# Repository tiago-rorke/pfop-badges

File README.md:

# Badges from Other Planets

I made these supercapacitor powered badges for [Nowhere 2019](https://www.goingnowhere.org/), a regional burn near Zaragoza, Spain, for our fledgling barrio "People from Other Planets".

I wanted to try to use supercapacitors to avoid consuming hundreds of non-rechargeable coin cell batteries whilst keeping the design as simple as possible. Because 5V supercaps are considerably more expensive, I've used a pair of 2.5V caps in series, with a 2.5V zener across each cap to prevent overcharging.  Not sure of the safety of this, the small amount of the use these boards have seen so far haven't yet led to any explosions, but none-the-less **use these at your own risk!**

I settled on a pair of 4.7F caps in series as a balance between cost/size/capacity, which for these two example sketches seem to provide around an hour of interaction and blinking lights after about 1 min of charging.  Without PWM the LEDs I chose are blindingly bright, I would suggest using larger resistors or different LEDs.

There are two versions of the board, one with an eletret microphone and amplifier for reacting to sound, the other with a 2.2M resistor for doing capacitive touch sensing.

The charging circuit uses a mosfet and zener to switch on a green LED once the capacitors are fully charged.  I originally used a 5.1V zener which worked in the prototype circuit, but this didn't work with the zeners I put on the finished boards, maybe the 5.1V is a bit too high for usb voltages. I later experimented with some different values and eventually settled on a 3.9V zener that seemed to work well. Not sure why the zener voltage had to be so low, but the green LED would only start to turn on as the circuit approached the USB voltage.  The usb VBUS contact is split in two, to simultaneously connect a red led when the board is plugged in to charge, a hack which seems to work most of the time.  The capacitor inrush current is limited by a 1W resistor, which can get a bit toasty and should probably be bigger.

I made some adafruit inspired led-sequins, along with some sewable transistor break-outs, which are included in the board layouts.

The silkscreen designs on the back of the boards are by fellow bairro member [Luke Andrews](http://lukeandrewsdesign.com/), and the PFOP logo is by the barrio lead [Rob Allison](http://www.robertallison.co.uk/).

We also disassembled a bunch of old laptop batteries, removed any good cells and put them into [empty powerbanks](https://www.aliexpress.com/item/32966395604.html) to provide charging units for the badges, and to use as power sources for other activities we did at the burn in our desert makerspace :).

## BOM

| | | qty |
|---|---|---|
| capacitors 4.7F | [farnell](https://pt.farnell.com/samxon/dre475s0eg20rrdap/cap-4-7f-2-5v-double-layer-radial/dp/2800103) | 2 |
| attiny45 | [mouser](https://pt.mouser.com/ProductDetail/Microchip-Technology-Atmel/ATTINY45-20XU?qs=sGAEpiMZZMvqv2n3s2xjsQTu%2F4bUyWdjf4Rc8T7jfeQ%3D) | 1 |
| white leds | [TME](https://www.tme.eu/pt/en/details/ll-r3014w-w5m-q10/smd-white-leds/lucky-light/) | 3 |
| red led | [TME](https://www.tme.eu/pt/en/details/ll-s172sc-2s/smd-colour-leds/lucky-light/) | 1 |
| green led | [TME](https://www.tme.eu/pt/en/details/el17-215sygc_53/smd-colour-leds/everlight/) | 1 |
| 3.3v regulator | [TME](https://www.tme.eu/pt/en/details/ap7313-33srg-7/ldo-unregulated-voltage-regulators/diodes-incorporated/) | 1 |
| 2.7v zener | [TME](https://www.tme.eu/pt/en/details/tzmb2v7-gs08/smd-zener-diodes/vishay/) | 2 |
| 3.9v zener | [TME](https://www.tme.eu/pt/en/details/bzv55c3v9-lge/smd-zener-diodes/luguang-electronic/bzv55c3v9/) | 1 |
| 2n7000 mosfet | [TME](https://www.tme.eu/pt/en/details/2n7002lt1g/smd-n-channel-transistors/on-semiconductor/) | 1 |
| resistor power 5.6R 1W | [TME](https://www.tme.eu/pt/en/details/smd2512-5r6/2512-smd-resistors/royal-ohm/25121wj056jt4e/) | 1 |
| resistor led 100R | [TME](https://www.tme.eu/pt/en/details/rc0805fr-07100r/0805-smd-resistors/yageo/rc0805fr-07100rl/) | 5 |
| resistor 10k | [TME](https://www.tme.eu/pt/en/details/smd0805-10k-1%25/0805-smd-resistors/royal-ohm/0805s8f1002t5e/) | 1 |
| *touch version* | | |
| resistor 2.2M | [TME](https://www.tme.eu/pt/en/details/smd0805-2m2/0805-smd-resistors/royal-ohm/0805s8j0225t5e/) | 1 |
| *sound version* | | |
| electret microphone | [aliexpress](https://www.aliexpress.com/item/10pcs-bag-4-5-2-2mm-condenser-electret-microphone-pickup-52DB/32262612470.html?spm=2114.search0104.3.2.36823c86ZRhB5p&ws_ab_test=searchweb0_0,searchweb201602_7_10065_10068_319_10059_10884_317_10887_10696_321_322_10084_453_10083_454_10103_10618_10304_10307_10820_10301_10821_537_536,searchweb201603_52,ppcSwitch_0&algo_expid=e5ac956f-4788-4c7e-8c49-3e065ae08252-0&algo_pvid=e5ac956f-4788-4c7e-8c49-3e065ae08252) | 1 |
| bc847 transistor | [TME](https://www.tme.eu/pt/en/details/bc847be6327/npn-smd-transistors/infineon-technologies/) | 1 |
| resistor 10k | [TME](https://www.tme.eu/pt/en/details/smd0805-10k-1%25/0805-smd-resistors/royal-ohm/0805s8f1002t5e/) | 1 |
| resistor 100k | [TME](https://www.tme.eu/pt/en/details/crcw0805100kfktabc/0805-smd-resistors/vishay/) | 1 |
| cap 0.1uF | [TME](https://www.tme.eu/pt/en/details/cc0805krx7r9104/0805-mlcc-smd-capacitors/yageo/cc0805krx7r9bb104/) | 1 |

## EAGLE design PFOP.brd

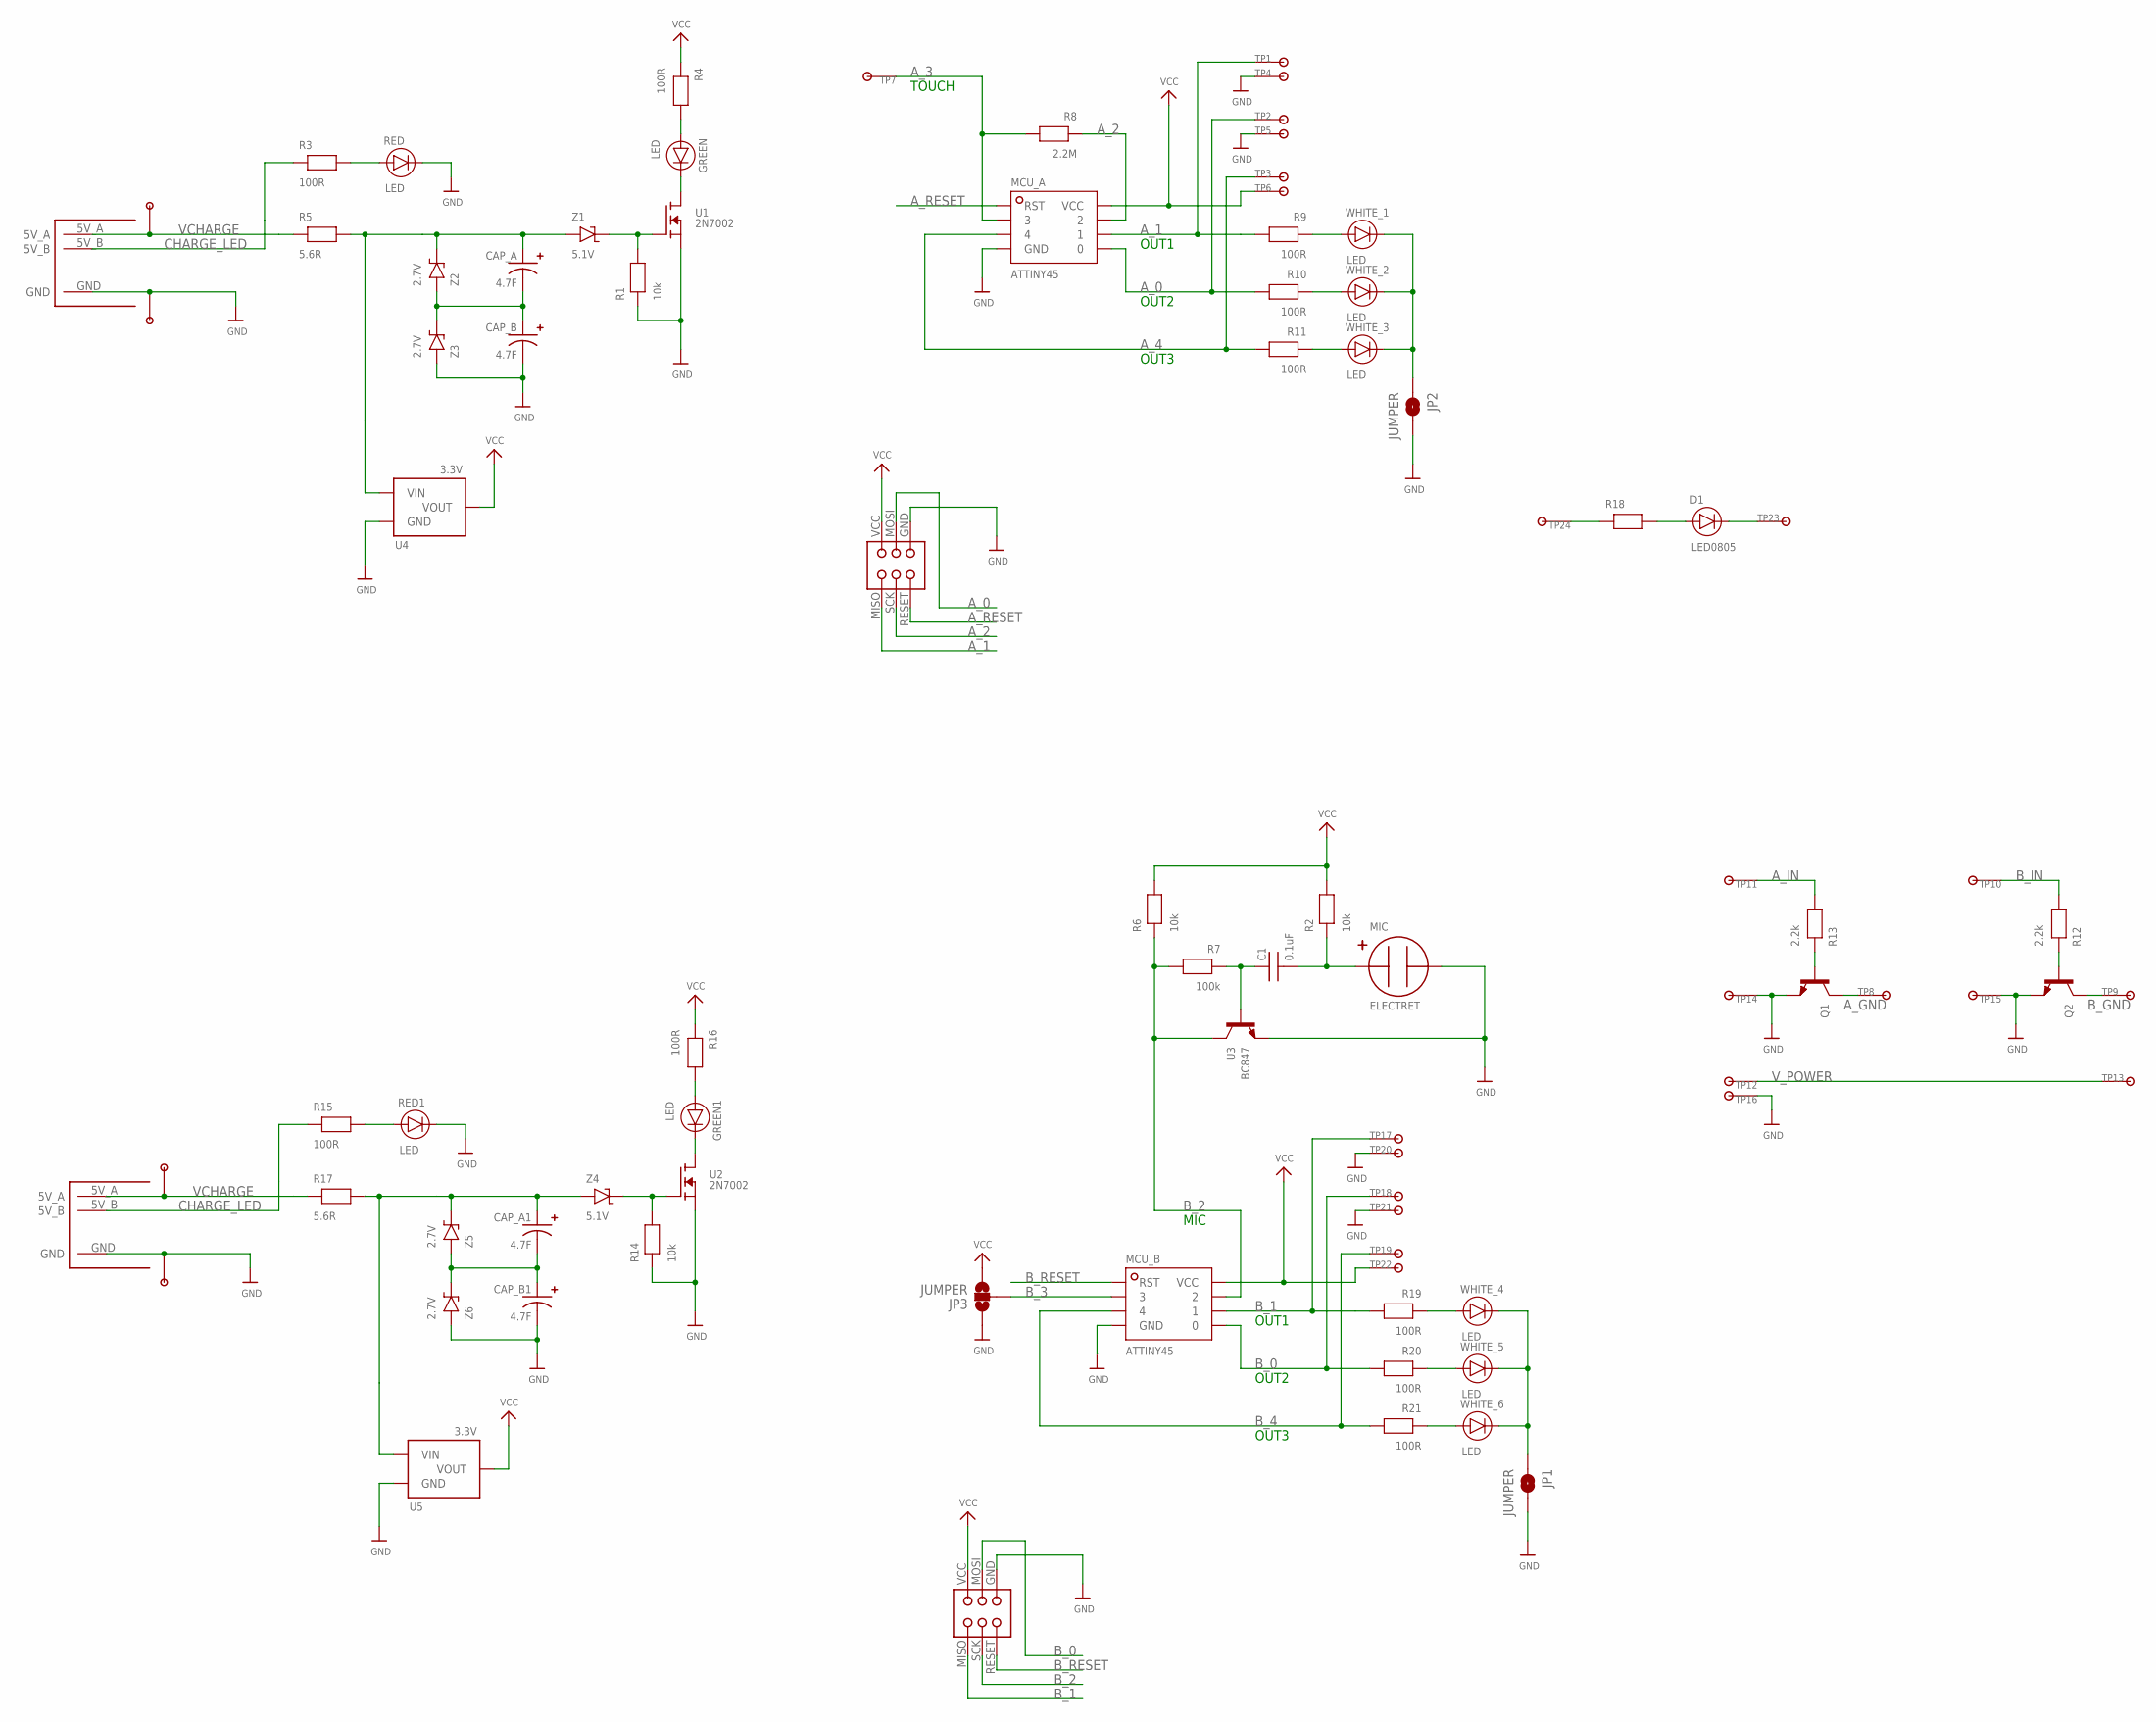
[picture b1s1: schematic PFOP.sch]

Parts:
C1: 0.1uF; 0805
CAP_A, CAP_A1: 4.7F; SUPERCAP_2.7V-4.7F
CAP_B, CAP_B1: 4.7F; SUPERCAP_2.7V-4.7F
D1: LED0805; 0805_LED
GREEN, GREEN1: LED; 0805_LED
J1, J2: ISP_HEADER
JP1, JP2: JUMPER; SMT-JUMPER_2_NO_NO-SILK
JP3: JUMPER; SMT-JUMPER_3_NO_NO-SILK
MCU_A: ATTINY45; TSSOP-8
MCU_B: ATTINY45; TSSOP-8
MIC: ELECTRET; ELECTRET_4.5MM
Q1, Q2: POWER_TRANSISTOR
R1, R2, R6, R14: 10k; 0805
R3, R4, R9, R10, R11, R15, R16, R19, R20, R21: 100R; 0805
R5, R17: 5.6R; 2512
R7: 100k; 0805
R8: 2.2M; 0805
R12, R13: 2.2k; 0805
R18: RESISTOR; 0805
RED, RED1: LED; 0805_LED
TP1, TP2, TP3, TP4, TP5, TP6, TP8, TP9, TP10, TP11, TP12, TP13, TP14, TP15, TP16, TP17, TP18, TP19, TP20, TP21, TP22: SEWTAPBIG; BIGTAP
TP7: SEWTAP; BIGTAP_TOUCH
TP23, TP24: SEWTAPSEQUIN; SEQUIN_TERMINAL
U1, U2: 2N7002; SOT23
U3: BC847; SOT23
U4, U5: 3.3V; SOT23
U$1, U$4: USB_CONN_POWER
U$2, U$3, U$5, U$6: 1PIN
WHITE_1, WHITE_2, WHITE_3, WHITE_4, WHITE_5, WHITE_6: LED; PLCC-2_LED
Z1, Z4: 5.1V; MINIMELF
Z2, Z3, Z5, Z6: 2.7V; MINIMELF

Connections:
A_0: J1.MOSI, MCU_A.5 (0), R10.2, TP2.P$1
A_1: J1.MISO, MCU_A.6 (1), R9.2, TP1.P$1
A_2: J1.SCK, MCU_A.7 (2), R8.1
A_3: MCU_A.2 (3), R8.2, TP7.P$1
A_4: MCU_A.3 (4), R11.2, TP3.P$1
A_GND: Q1.C, TP8.P$1
A_IN: R13.2, TP11.P$1
A_RESET: J1.RESET, MCU_A.1 (RST)
B_0: J2.MOSI, MCU_B.5 (0), R20.2, TP18.P$1
B_1: J2.MISO, MCU_B.6 (1), R19.2, TP17.P$1
B_2: J2.SCK, MCU_B.7 (2), R6.1, R7.2, U3.3 (C)
B_3: JP3.2, MCU_B.2 (3)
B_4: MCU_B.3 (4), R21.2, TP19.P$1
B_GND: Q2.C, TP9.P$1
B_IN: R12.2, TP10.P$1
B_RESET: J2.RESET, MCU_B.1 (RST)
CHARGE_LED: R3.1, R15.1, U$1.5V_B, U$4.5V_B
GND: CAP_B.-, CAP_B1.-, J1.GND, J2.GND, JP1.2, JP2.2, JP3.1, MCU_A.4 (GND), MCU_B.4 (GND), MIC.- (V-), Q1.E, Q2.E, R1.1, R14.1, RED.-, RED1.-, TP4.P$1, TP5.P$1, TP14.P$1, TP15.P$1, TP16.P$1, TP20.P$1, TP21.P$1, U1.2 (S), U2.2 (S), U3.2 (E), U4.1 (GND), U5.1 (GND), U$1.GND, U$3.P$1, U$4.GND, U$6.P$1, Z3.1, Z6.1
unnamed: R3.2, RED.+
unnamed: R15.2, RED1.+
unnamed: R1.2, U1.1 (G), Z1.2
unnamed: GREEN.-, U1.3 (D)
unnamed: CAP_A.-, CAP_B.+, Z2.1, Z3.2
unnamed: R14.2, U2.1 (G), Z4.2
unnamed: GREEN.+, R4.2
unnamed: C1.2, MIC.+ (V+), R2.1
unnamed: GREEN1.-, U2.3 (D)
unnamed: C1.1, R7.1, U3.1 (B)
unnamed: Q2.B, R12.1
unnamed: CAP_A1.-, CAP_B1.+, Z5.1, Z6.2
unnamed: GREEN1.+, R16.2
unnamed: R9.1, WHITE_1.+
unnamed: R10.1, WHITE_2.+
unnamed: R11.1, WHITE_3.+
unnamed: JP2.1, WHITE_1.-, WHITE_2.-, WHITE_3.-
unnamed: R19.1, WHITE_4.+
unnamed: R20.1, WHITE_5.+
unnamed: Q1.B, R13.1
unnamed: R21.1, WHITE_6.+
unnamed: JP1.1, WHITE_4.-, WHITE_5.-, WHITE_6.-
unnamed: R18.1, TP24.P$1
unnamed: D1.+, R18.2
unnamed: D1.-, TP23.P$1
VCAP: CAP_A.+, R5.2, U4.3 (VIN), Z1.1, Z2.2
VCAP1: CAP_A1.+, R17.2, U5.3 (VIN), Z4.1, Z5.2
VCC: J1.VCC, J2.VCC, JP3.3, MCU_A.8 (VCC), MCU_B.8 (VCC), R2.2, R4.1, R6.2, R16.1, TP6.P$1, TP22.P$1, U4.2 (VOUT), U5.2 (VOUT)
VCHARGE: R5.1, R17.1, U$1.5V_A, U$2.P$1, U$4.5V_A, U$5.P$1
V_POWER: TP12.P$1, TP13.P$1

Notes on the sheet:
TOUCH
OUT1
OUT2
OUT3
MIC

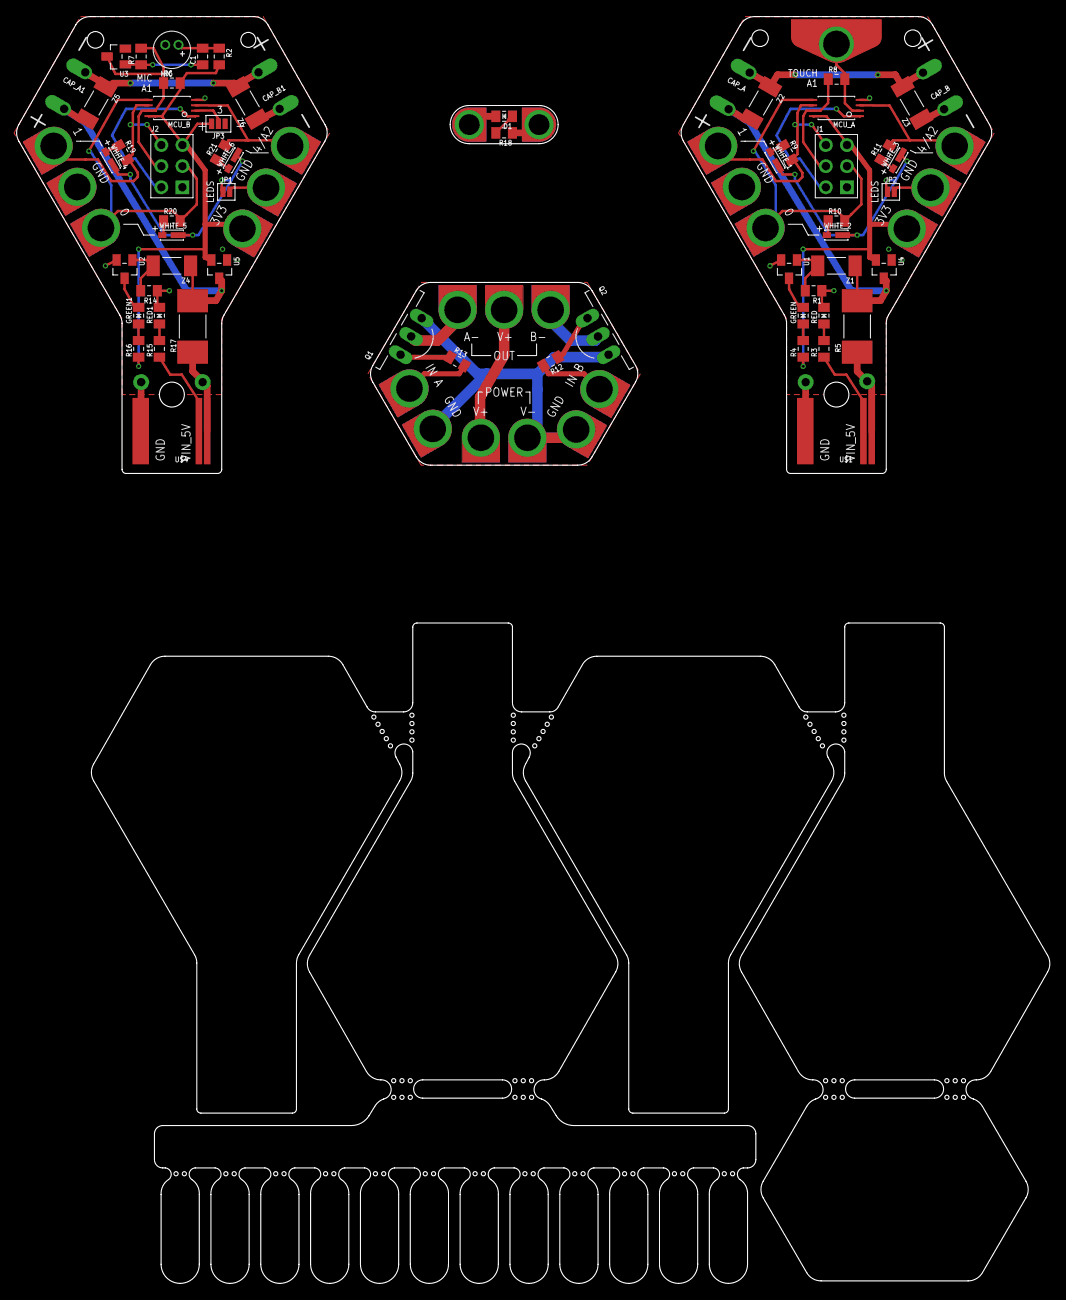
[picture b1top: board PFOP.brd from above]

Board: 2 copper layers, 124.4 x 152.5 mm, 88 parts (0 on the bottom side), 48 nets.

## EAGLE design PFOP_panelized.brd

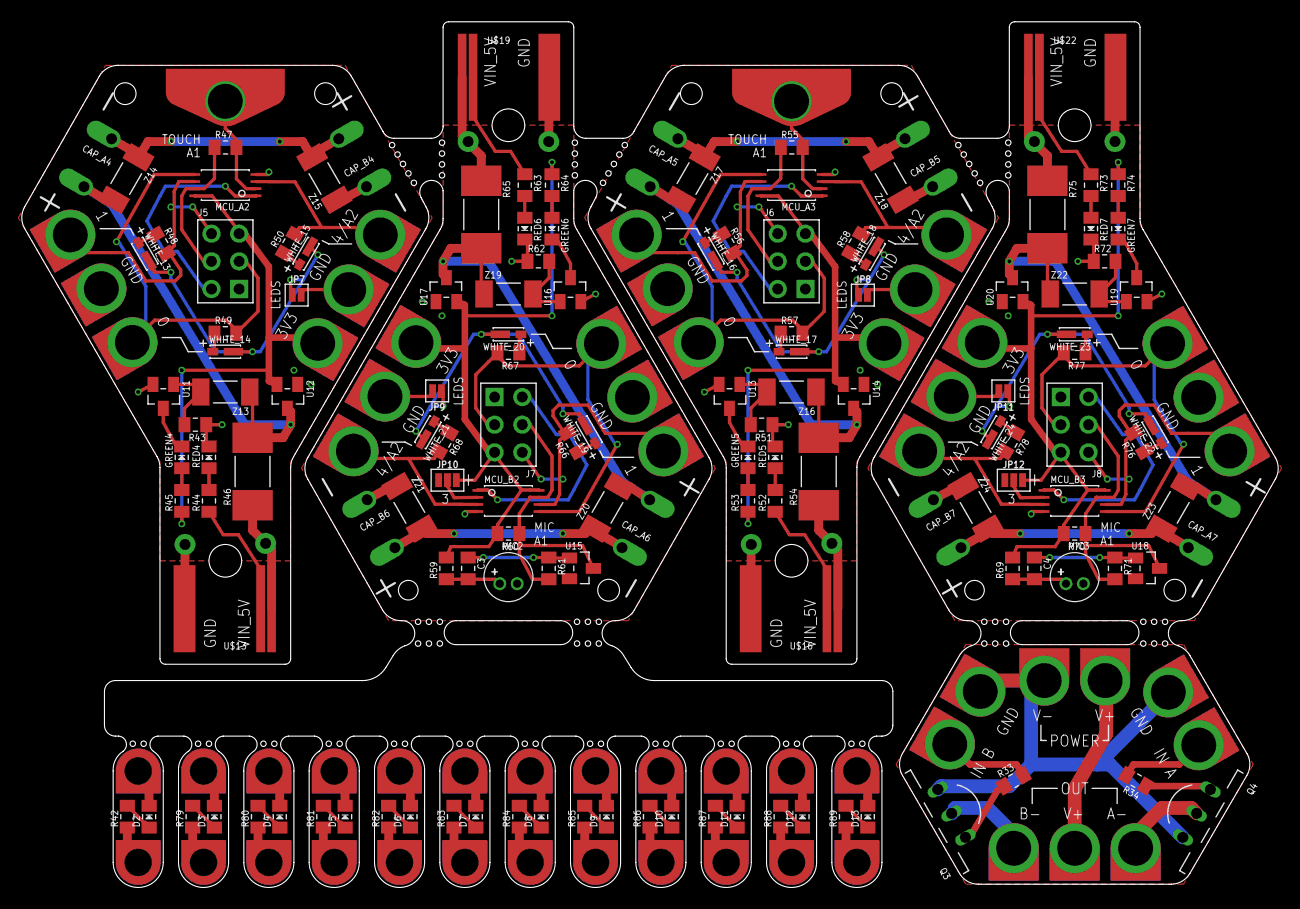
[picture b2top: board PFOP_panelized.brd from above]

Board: 2 copper layers, 115.4 x 79.5 mm, 203 parts (0 on the bottom side), 128 nets.

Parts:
C3, C4: 0.1uF; 0805
CAP_A4, CAP_A5, CAP_A6, CAP_A7: 4.7F; SUPERCAP_2.7V-4.7F
CAP_B4, CAP_B5, CAP_B6, CAP_B7: 4.7F; SUPERCAP_2.7V-4.7F
D2, D3, D4, D5, D6, D7, D8, D9, D10, D11, D12, D13: LED0805; 0805_LED
GREEN4, GREEN5, GREEN6, GREEN7: LED; 0805_LED
J5, J6, J7, J8: ISP_HEADER
JP7, JP8, JP9, JP11: JUMPER; SMT-JUMPER_2_NO_NO-SILK
JP10, JP12: JUMPER; SMT-JUMPER_3_NO_NO-SILK
MCU_A2, MCU_A3: ATTINY45; TSSOP-8
MCU_B2, MCU_B3: ATTINY45; TSSOP-8
MIC2, MIC3: ELECTRET; ELECTRET_4.5MM
Q3, Q4: POWER_TRANSISTOR
R33, R34: 2.2k; 0805
R42, R79, R80, R81, R82, R83, R84, R85, R86, R87, R88, R89: 0805
R43, R51, R59, R60, R62, R69, R70, R72: 10k; 0805
R44, R45, R48, R49, R50, R52, R53, R56, R57, R58, R63, R64, R66, R67, R68, R73, R74, R76, R77, R78: 100R; 0805
R46, R54, R65, R75: 5.6R; 2512
R47, R55: 2.2M; 0805
R61, R71: 100k; 0805
RED4, RED5, RED6, RED7: LED; 0805_LED
TP32, TP33, TP34, TP35, TP36, TP37, TP38, TP39, TP40, TP49, TP50, TP51, TP52, TP53, TP54, TP56, TP57, TP58, TP59, TP60, TP61, TP63, TP64, TP65, TP66, TP67, TP68, TP69, TP70, TP71, TP72, TP73, TP74: SEWTAPBIG; BIGTAP
TP47, TP48, TP75, TP76, TP77, TP78, TP79, TP80, TP81, TP82, TP83, TP84, TP85, TP86, TP87, TP88, TP89, TP90, TP91, TP92, TP93, TP94, TP95, TP96: SEWTAPSEQUIN; SEQUIN_TERMINAL
TP55, TP62: SEWTAP; BIGTAP_TOUCH
U11, U13, U16, U19: 2N7002; SOT23
U12, U14, U17, U20: 3.3V; SOT23
U15, U18: BC847; SOT23
U$13, U$16, U$19, U$22: USB_CONN_POWER
U$14, U$15, U$17, U$18, U$20, U$21, U$23, U$24: 1PIN
WHITE_13, WHITE_14, WHITE_15, WHITE_16, WHITE_17, WHITE_18, WHITE_19, WHITE_20, WHITE_21, WHITE_22, WHITE_23, WHITE_24: LED; PLCC-2_LED
Z13, Z16, Z19, Z22: 5.1V; MINIMELF
Z14, Z15, Z17, Z18, Z20, Z21, Z23, Z24: 2.7V; MINIMELF

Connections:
A_10: J5.SCK, MCU_A2.7, R47.1
A_11: MCU_A2.2, R47.2, TP55.P$1
A_12: MCU_A2.3, R50.2, TP51.P$1
A_13: J5.MOSI, MCU_A2.5, R49.2, TP50.P$1
A_14: J5.MISO, MCU_A2.6, R48.2, TP49.P$1
A_15: J6.SCK, MCU_A3.7, R55.1
A_16: MCU_A3.2, R55.2, TP62.P$1
A_17: MCU_A3.3, R58.2, TP58.P$1
A_18: J6.MOSI, MCU_A3.5, R57.2, TP57.P$1
A_19: J6.MISO, MCU_A3.6, R56.2, TP56.P$1
A_GND1: Q4.C, TP32.P$1
A_IN1: R34.2, TP35.P$1
A_RESET2: J5.RESET, MCU_A2.1
A_RESET3: J6.RESET, MCU_A3.1
B_10: J7.SCK, MCU_B2.7, R60.1, R61.2, U15.3
B_11: J7.MOSI, MCU_B2.5, R67.2, TP64.P$1
B_12: J7.MISO, MCU_B2.6, R66.2, TP63.P$1
B_13: MCU_B2.3, R68.2, TP65.P$1
B_14: JP10.2, MCU_B2.2
B_15: J8.SCK, MCU_B3.7, R70.1, R71.2, U18.3
B_16: J8.MOSI, MCU_B3.5, R77.2, TP70.P$1
B_17: J8.MISO, MCU_B3.6, R76.2, TP69.P$1
B_18: MCU_B3.3, R78.2, TP71.P$1
B_19: JP12.2, MCU_B3.2
B_GND1: Q3.C, TP33.P$1
B_IN1: R33.2, TP34.P$1
B_RESET2: J7.RESET, MCU_B2.1
B_RESET3: J8.RESET, MCU_B3.1
CHARGE_LED2: R44.1, U$13.5V_B
CHARGE_LED3: R52.1, U$16.5V_B
CHARGE_LED4: R63.1, U$19.5V_B
CHARGE_LED5: R73.1, U$22.5V_B
GND2: CAP_B4.-, J5.GND, JP7.2, MCU_A2.4, R43.1, RED4.-, TP52.P$1, TP53.P$1, U11.2, U12.1, U$13.GND, U$15.P$1, Z15.1
GND3: CAP_B5.-, J6.GND, JP8.2, MCU_A3.4, R51.1, RED5.-, TP59.P$1, TP60.P$1, U13.2, U14.1, U$16.GND, U$18.P$1, Z18.1
GND4: CAP_B6.-, J7.GND, JP9.2, JP10.1, MCU_B2.4, MIC2.-, R62.1, RED6.-, TP66.P$1, TP67.P$1, U15.2, U16.2, U17.1, U$19.GND, U$21.P$1, Z21.1
GND5: CAP_B7.-, J8.GND, JP11.2, JP12.1, MCU_B3.4, MIC3.-, R72.1, RED7.-, TP72.P$1, TP73.P$1, U18.2, U19.2, U20.1, U$22.GND, U$24.P$1, Z24.1
unnamed: Q3.B, R33.1
unnamed: Q4.B, R34.1
unnamed: R42.1, TP48.P$1
unnamed: D2.+, R42.2
unnamed: D2.-, TP47.P$1
unnamed: R44.2, RED4.+
unnamed: R43.2, U11.1, Z13.2
unnamed: GREEN4.-, U11.3
unnamed: CAP_A4.-, CAP_B4.+, Z14.1, Z15.2
unnamed: GREEN4.+, R45.2
unnamed: R48.1, WHITE_13.+
unnamed: R49.1, WHITE_14.+
unnamed: R50.1, WHITE_15.+
unnamed: JP7.1, WHITE_13.-, WHITE_14.-, WHITE_15.-
unnamed: R52.2, RED5.+
unnamed: R51.2, U13.1, Z16.2
unnamed: GREEN5.-, U13.3
unnamed: CAP_A5.-, CAP_B5.+, Z17.1, Z18.2
unnamed: GREEN5.+, R53.2
unnamed: R56.1, WHITE_16.+
unnamed: R57.1, WHITE_17.+
unnamed: R58.1, WHITE_18.+
unnamed: JP8.1, WHITE_16.-, WHITE_17.-, WHITE_18.-
unnamed: C3.2, MIC2.+, R59.1
unnamed: C3.1, R61.1, U15.1
unnamed: R63.2, RED6.+
unnamed: R62.2, U16.1, Z19.2
unnamed: GREEN6.-, U16.3
unnamed: CAP_A6.-, CAP_B6.+, Z20.1, Z21.2
unnamed: GREEN6.+, R64.2
unnamed: R66.1, WHITE_19.+
unnamed: R67.1, WHITE_20.+
unnamed: R68.1, WHITE_21.+
unnamed: JP9.1, WHITE_19.-, WHITE_20.-, WHITE_21.-
unnamed: C4.2, MIC3.+, R69.1
unnamed: C4.1, R71.1, U18.1
unnamed: R73.2, RED7.+
unnamed: R72.2, U19.1, Z22.2
unnamed: GREEN7.-, U19.3
unnamed: CAP_A7.-, CAP_B7.+, Z23.1, Z24.2
unnamed: GREEN7.+, R74.2
unnamed: R76.1, WHITE_22.+
unnamed: R77.1, WHITE_23.+
unnamed: R78.1, WHITE_24.+
unnamed: JP11.1, WHITE_22.-, WHITE_23.-, WHITE_24.-
unnamed: R79.1, TP76.P$1
unnamed: D3.+, R79.2
unnamed: D3.-, TP75.P$1
unnamed: R80.1, TP78.P$1
unnamed: D4.+, R80.2
unnamed: D4.-, TP77.P$1
unnamed: R81.1, TP80.P$1
unnamed: D5.+, R81.2
unnamed: D5.-, TP79.P$1
unnamed: R82.1, TP82.P$1
unnamed: D6.+, R82.2
unnamed: D6.-, TP81.P$1
unnamed: R83.1, TP84.P$1
unnamed: D7.+, R83.2
unnamed: D7.-, TP83.P$1
unnamed: R84.1, TP86.P$1
unnamed: D8.+, R84.2
unnamed: D8.-, TP85.P$1
unnamed: R85.1, TP88.P$1
unnamed: D9.+, R85.2
unnamed: D9.-, TP87.P$1
unnamed: R86.1, TP90.P$1
unnamed: D10.+, R86.2
unnamed: D10.-, TP89.P$1
unnamed: R87.1, TP92.P$1
unnamed: D11.+, R87.2
unnamed: D11.-, TP91.P$1
unnamed: R88.1, TP94.P$1
unnamed: D12.+, R88.2
unnamed: D12.-, TP93.P$1
unnamed: R89.1, TP96.P$1
unnamed: D13.+, R89.2
unnamed: D13.-, TP95.P$1
S$8: Q3.E, Q4.E, TP38.P$1, TP39.P$1, TP40.P$1
VCAP4: CAP_A4.+, R46.2, U12.3, Z13.1, Z14.2
VCAP5: CAP_A5.+, R54.2, U14.3, Z16.1, Z17.2
VCAP6: CAP_A6.+, R65.2, U17.3, Z19.1, Z20.2
VCAP7: CAP_A7.+, R75.2, U20.3, Z22.1, Z23.2
VCC2: J5.VCC, MCU_A2.8, R45.1, TP54.P$1, U12.2
VCC3: J6.VCC, MCU_A3.8, R53.1, TP61.P$1, U14.2
VCC4: J7.VCC, JP10.3, MCU_B2.8, R59.2, R60.2, R64.1, TP68.P$1, U17.2
VCC5: J8.VCC, JP12.3, MCU_B3.8, R69.2, R70.2, R74.1, TP74.P$1, U20.2
VCHARGE2: R46.1, U$13.5V_A, U$14.P$1
VCHARGE3: R54.1, U$16.5V_A, U$17.P$1
VCHARGE4: R65.1, U$19.5V_A, U$20.P$1
VCHARGE5: R75.1, U$22.5V_A, U$23.P$1
V_POWER1: TP36.P$1, TP37.P$1

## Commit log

2020-03-21 readme edit
2020-03-21 readme edits
2020-03-21 add eagle lib
2020-03-22 add arduino sketches
